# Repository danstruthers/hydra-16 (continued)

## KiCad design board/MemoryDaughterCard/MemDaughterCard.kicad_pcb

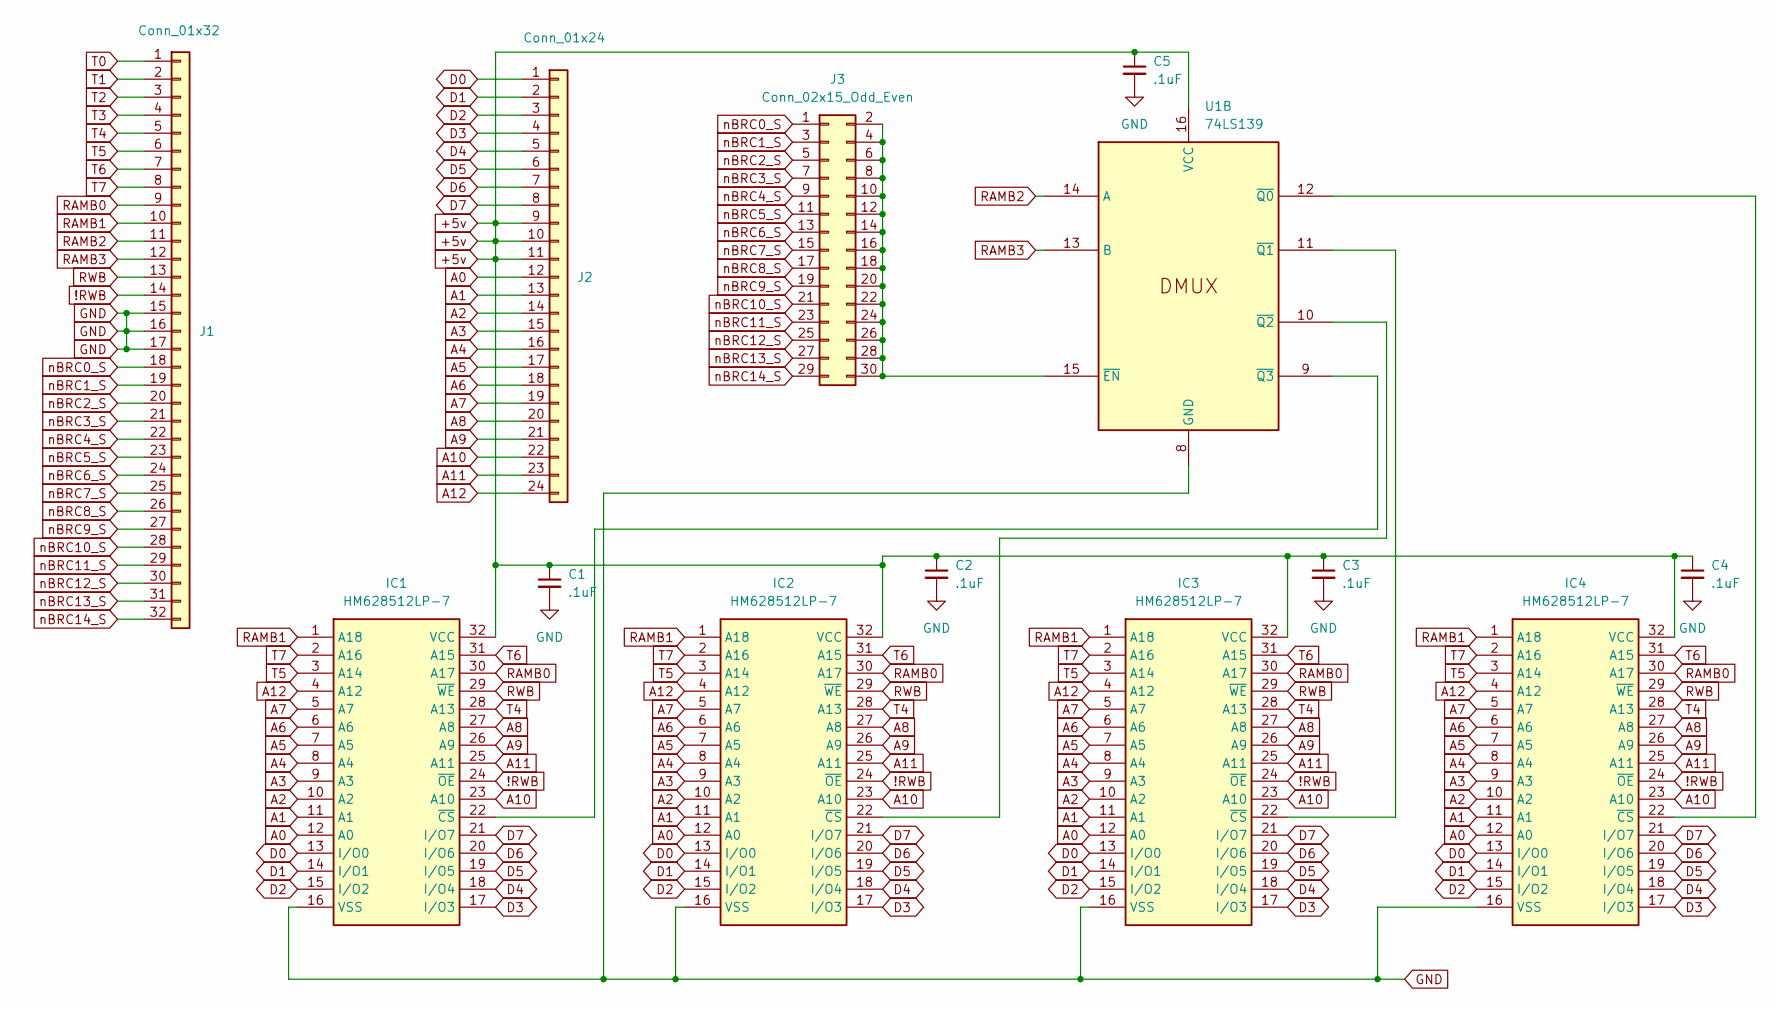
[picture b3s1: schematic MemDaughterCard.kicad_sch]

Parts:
C1, C2, C3, C4, C5: .1uF; C_Disc_D5.0mm_W2.5mm_P5.00mm
IC1, IC2, IC3, IC4: HM628512LP-7; DIP-32_W15.24mm_Socket_LongPads; Manufacturer_Part_Number HM628512LFP-7
J1: Conn_01x32; PinHeader_1x32_P2.54mm_Vertical
J2: Conn_01x24; PinHeader_1x24_P2.54mm_Vertical
J3: Conn_02x15_Odd_Even; PinHeader_2x15_P2.54mm_Vertical
U1: 74LS139; DIP-16_W7.62mm

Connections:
!RWB: IC1.24 (~OE), IC2.24 (~OE), IC3.24 (~OE), IC4.24 (~OE), J1.14
+5v: C1.1, C2.1, C3.1, C4.1, C5.1, IC1.32 (VCC), IC2.32 (VCC), IC3.32 (VCC), IC4.32 (VCC), J2.9, J2.10, J2.11, U1.16 (VCC)
A0: IC1.12 (A0), IC2.12 (A0), IC3.12 (A0), IC4.12 (A0), J2.12
A1: IC1.11 (A1), IC2.11 (A1), IC3.11 (A1), IC4.11 (A1), J2.13
A2: IC1.10 (A2), IC2.10 (A2), IC3.10 (A2), IC4.10 (A2), J2.14
A3: IC1.9 (A3), IC2.9 (A3), IC3.9 (A3), IC4.9 (A3), J2.15
A4: IC1.8 (A4), IC2.8 (A4), IC3.8 (A4), IC4.8 (A4), J2.16
A5: IC1.7 (A5), IC2.7 (A5), IC3.7 (A5), IC4.7 (A5), J2.17
A6: IC1.6 (A6), IC2.6 (A6), IC3.6 (A6), IC4.6 (A6), J2.18
A7: IC1.5 (A7), IC2.5 (A7), IC3.5 (A7), IC4.5 (A7), J2.19
A8: IC1.27 (A8), IC2.27 (A8), IC3.27 (A8), IC4.27 (A8), J2.20
A9: IC1.26 (A9), IC2.26 (A9), IC3.26 (A9), IC4.26 (A9), J2.21
A10: IC1.23 (A10), IC2.23 (A10), IC3.23 (A10), IC4.23 (A10), J2.22
A11: IC1.25 (A11), IC2.25 (A11), IC3.25 (A11), IC4.25 (A11), J2.23
A12: IC1.4 (A12), IC2.4 (A12), IC3.4 (A12), IC4.4 (A12), J2.24
D0: IC1.13 (I/O0), IC2.13 (I/O0), IC3.13 (I/O0), IC4.13 (I/O0), J2.1
D1: IC1.14 (I/O1), IC2.14 (I/O1), IC3.14 (I/O1), IC4.14 (I/O1), J2.2
D2: IC1.15 (I/O2), IC2.15 (I/O2), IC3.15 (I/O2), IC4.15 (I/O2), J2.3
D3: IC1.17 (I/O3), IC2.17 (I/O3), IC3.17 (I/O3), IC4.17 (I/O3), J2.4
D4: IC1.18 (I/O4), IC2.18 (I/O4), IC3.18 (I/O4), IC4.18 (I/O4), J2.5
D5: IC1.19 (I/O5), IC2.19 (I/O5), IC3.19 (I/O5), IC4.19 (I/O5), J2.6
D6: IC1.20 (I/O6), IC2.20 (I/O6), IC3.20 (I/O6), IC4.20 (I/O6), J2.7
D7: IC1.21 (I/O7), IC2.21 (I/O7), IC3.21 (I/O7), IC4.21 (I/O7), J2.8
GND: C1.2, C2.2, C3.2, C4.2, C5.2, IC1.16 (VSS), IC2.16 (VSS), IC3.16 (VSS), IC4.16 (VSS), J1.15, J1.16, J1.17, U1.8 (GND)
unnamed: IC1.22 (~CS), U1.9 (~Q3)
unnamed: IC2.22 (~CS), U1.10 (~Q2)
unnamed: IC3.22 (~CS), U1.11 (~Q1)
unnamed: IC4.22 (~CS), U1.12 (~Q0)
unnamed: J3.2, J3.4, J3.6, J3.8, J3.10, J3.12, J3.14, J3.16, J3.18, J3.20, J3.22, J3.24, J3.26, J3.28, J3.30, U1.15 (~EN)
RAMB0: IC1.30 (A17), IC2.30 (A17), IC3.30 (A17), IC4.30 (A17), J1.9
RAMB1: IC1.1 (A18), IC2.1 (A18), IC3.1 (A18), IC4.1 (A18), J1.10
RAMB2: J1.11, U1.14 (A)
RAMB3: J1.12, U1.13 (B)
RWB: IC1.29 (~WE), IC2.29 (~WE), IC3.29 (~WE), IC4.29 (~WE), J1.13
T0: J1.1
T1: J1.2
T2: J1.3
T3: J1.4
T4: IC1.28 (A13), IC2.28 (A13), IC3.28 (A13), IC4.28 (A13), J1.5
T5: IC1.3 (A14), IC2.3 (A14), IC3.3 (A14), IC4.3 (A14), J1.6
T6: IC1.31 (A15), IC2.31 (A15), IC3.31 (A15), IC4.31 (A15), J1.7
T7: IC1.2 (A16), IC2.2 (A16), IC3.2 (A16), IC4.2 (A16), J1.8
nBRC0_S: J1.18, J3.1
nBRC1_S: J1.19, J3.3
nBRC2_S: J1.20, J3.5
nBRC3_S: J1.21, J3.7
nBRC4_S: J1.22, J3.9
nBRC5_S: J1.23, J3.11
nBRC6_S: J1.24, J3.13
nBRC7_S: J1.25, J3.15
nBRC8_S: J1.26, J3.17
nBRC9_S: J1.27, J3.19
nBRC10_S: J1.28, J3.21
nBRC11_S: J1.29, J3.23
nBRC12_S: J1.30, J3.25
nBRC13_S: J1.31, J3.27
nBRC14_S: J1.32, J3.29

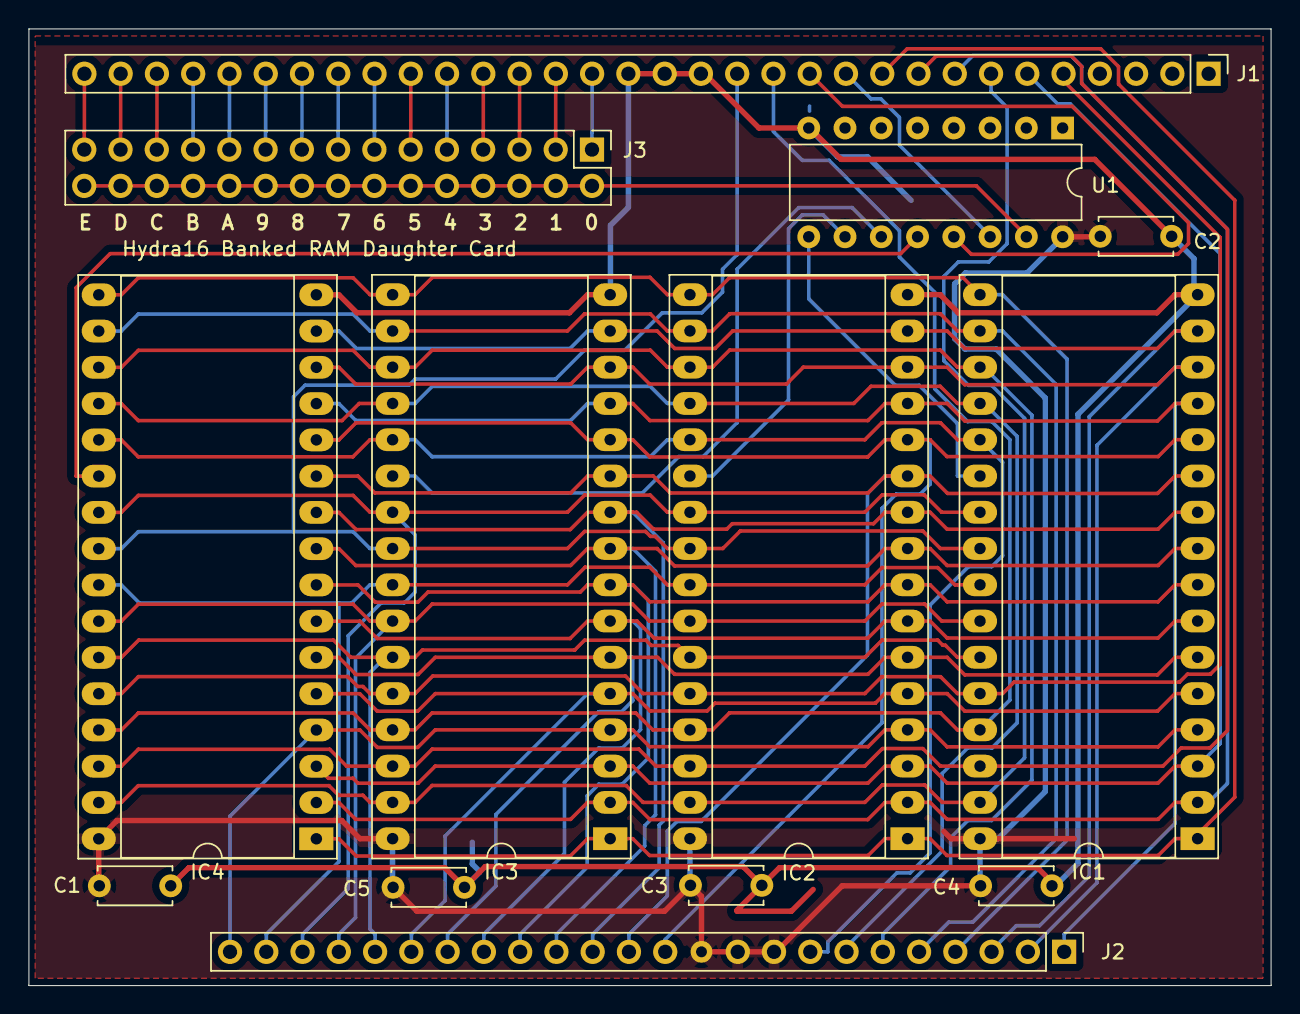
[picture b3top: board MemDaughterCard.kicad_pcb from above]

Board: 2 copper layers, 87.0 x 67.0 mm, 13 parts (0 on the bottom side), 53 nets.

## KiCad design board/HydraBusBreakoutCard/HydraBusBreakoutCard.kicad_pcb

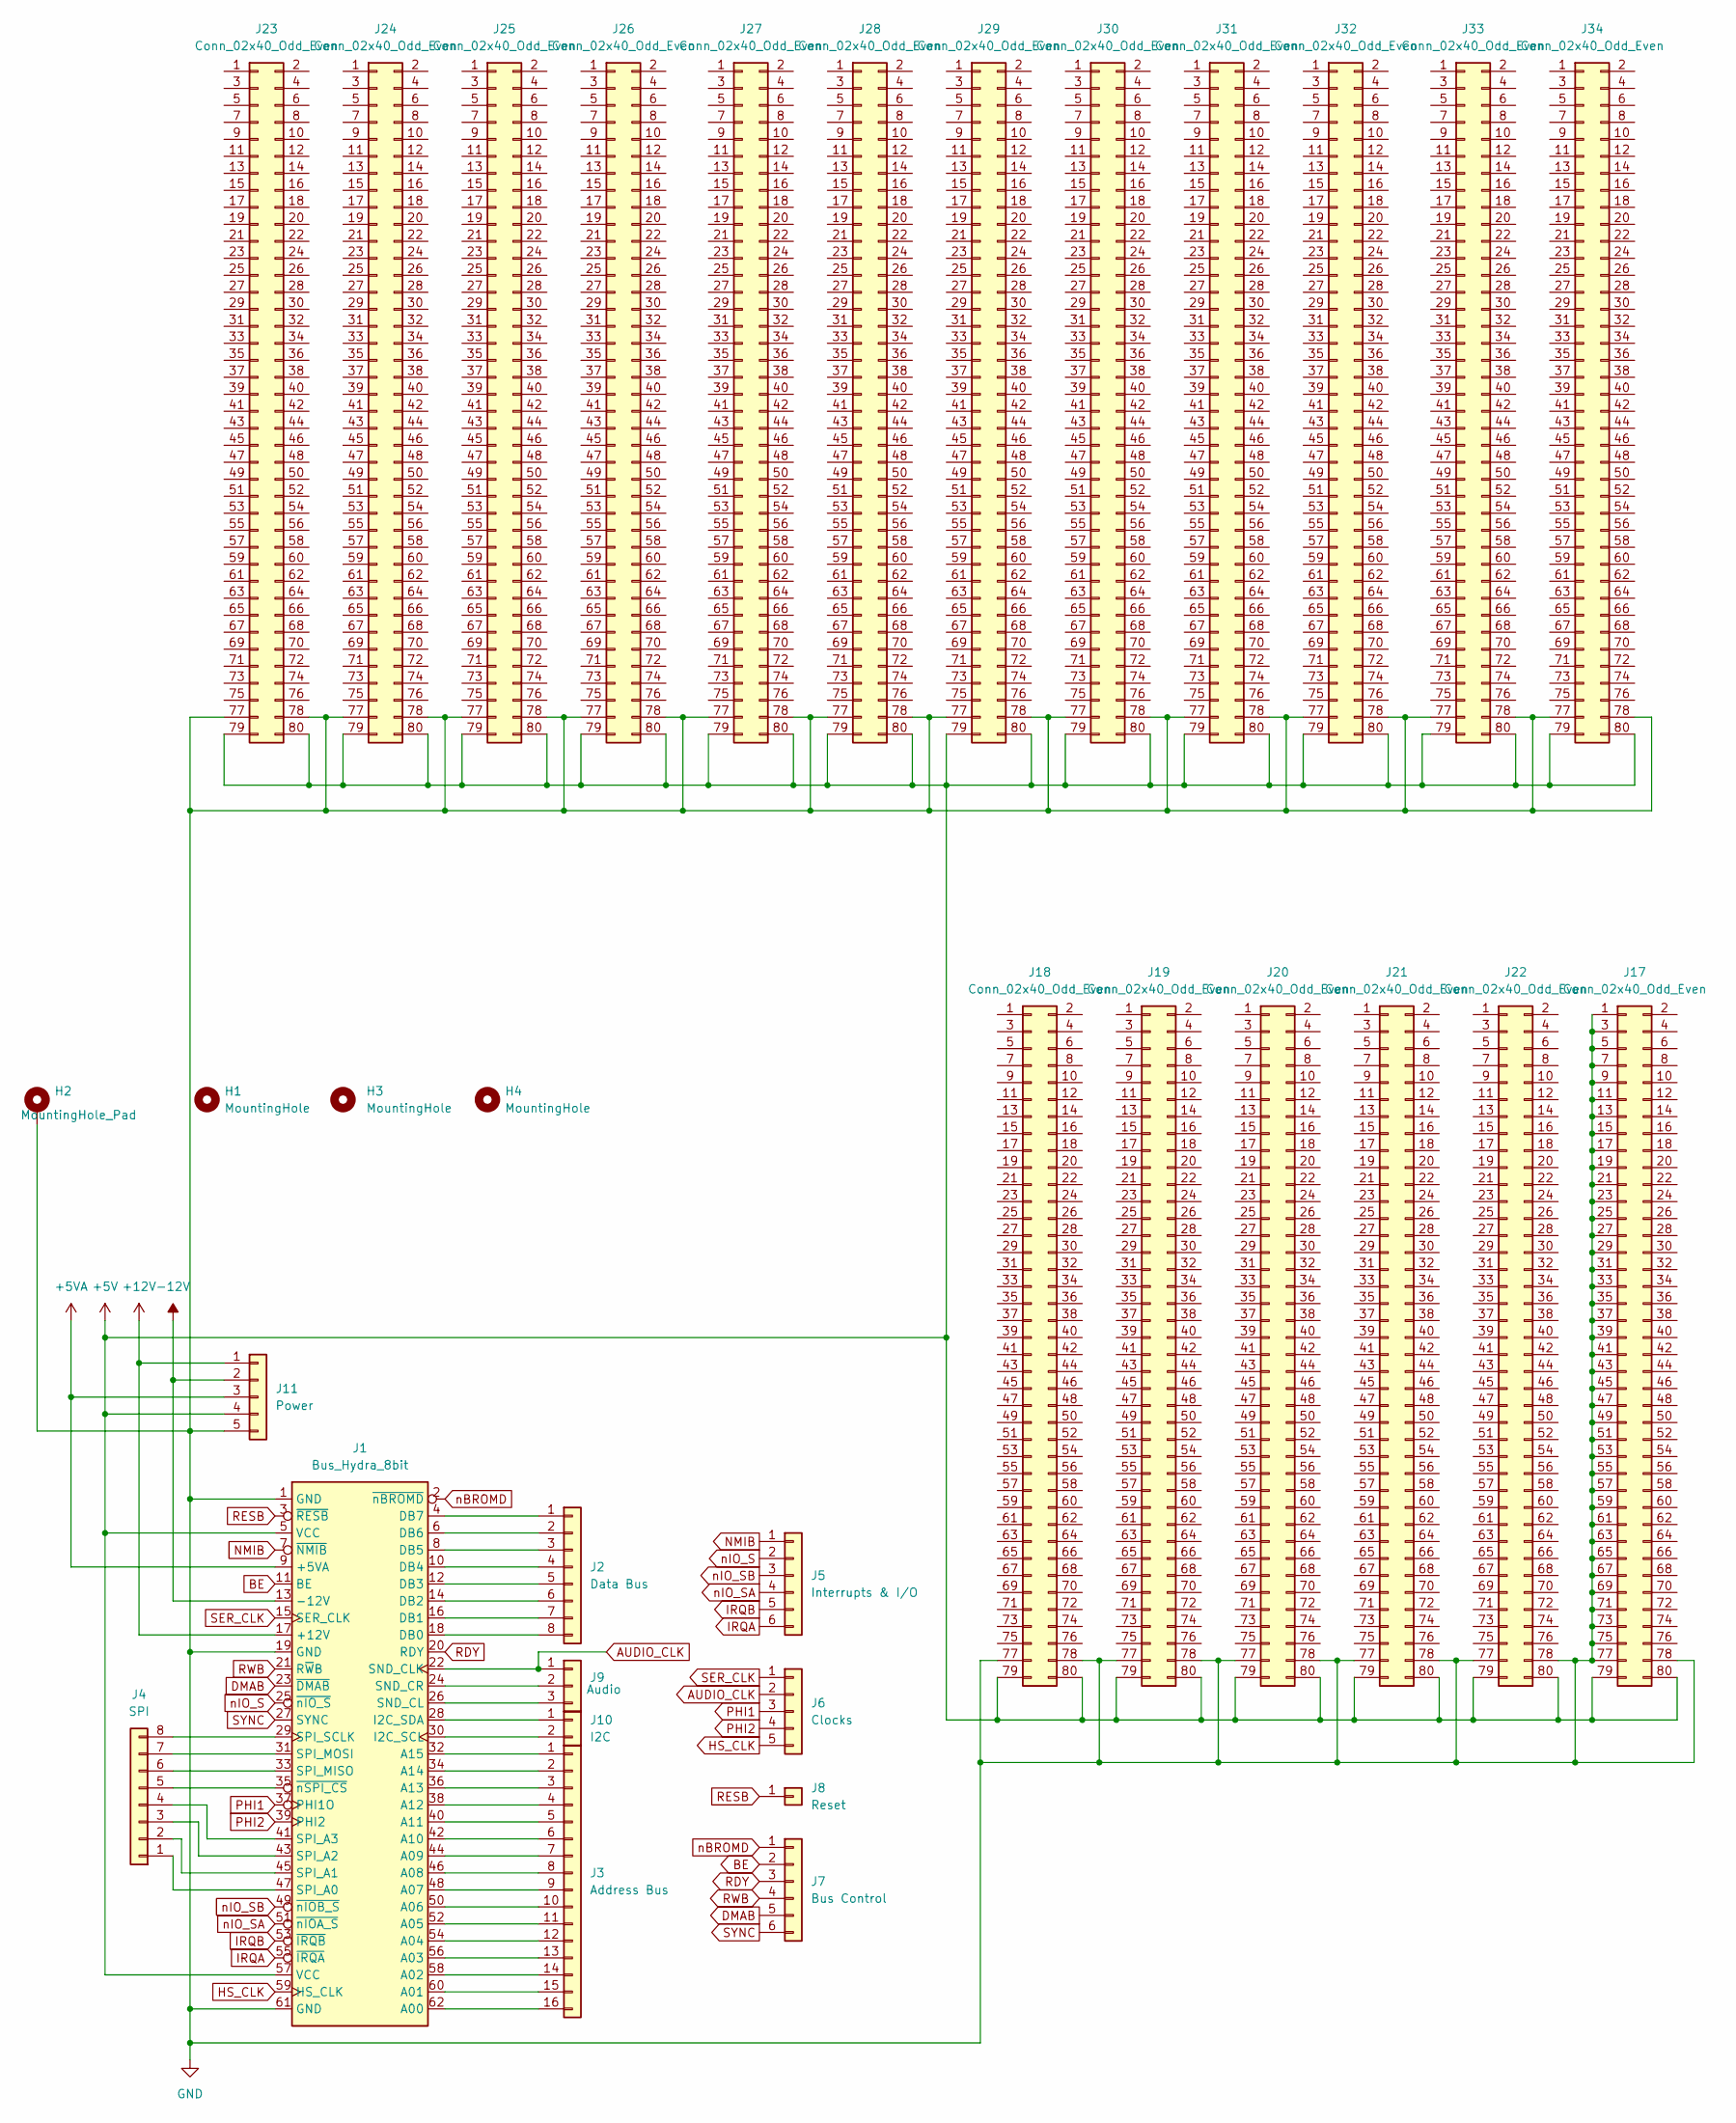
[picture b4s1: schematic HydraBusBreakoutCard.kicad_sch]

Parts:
H1, H3, H4: MountingHole; MountingHole_3.2mm_M3
H2: MountingHole_Pad; MountingHole_3.2mm_M3_ISO7380_Pad_TopBottom
J1: Bus_Hydra_8bit; BUS_Hydra_8Bit
J2: Data Bus; PinHeader_1x08_P2.54mm_Vertical
J3: Address Bus; PinHeader_1x16_P2.54mm_Vertical
J4: SPI; PinHeader_1x08_P2.54mm_Vertical
J5: Interrupts & I/O; PinHeader_1x06_P2.54mm_Vertical
J6: Clocks; PinHeader_1x05_P2.54mm_Vertical
J7: Bus Control; PinHeader_1x06_P2.54mm_Vertical
J8: Reset; PinHeader_1x01_P2.54mm_Vertical
J9: Audio; PinHeader_1x03_P2.54mm_Vertical
J10: I2C; PinHeader_1x02_P2.54mm_Vertical
J11: Power; PinHeader_1x05_P2.54mm_Vertical
J17, J18, J19, J20, J21, J22, J23, J24, J25, J26, J27, J28, J29, J30, J31, J32, J33, J34: Conn_02x40_Odd_Even; PinHeader_2x40_P2.54mm_Vertical

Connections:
+5V: J1.5 (VCC), J1.57 (VCC), J11.4, J17.79, J17.80, J18.79, J18.80, J19.79, J19.80, J20.79, J20.80, J21.79, J21.80, J22.79, J22.80, J23.79, J23.80, J24.79, J24.80, J25.79, J25.80, J26.79, J26.80, J27.79, J27.80, J28.79, J28.80, J29.79, J29.80, J30.79, J30.80, J31.79, J31.80, J32.79, J32.80, J33.79, J33.80, J34.79, J34.80
+5VA: J1.9 (+5VA), J11.3
+12V: J1.17 (+12V), J11.1
-12V: J1.13 (-12V), J11.2
AUDIO_CLK: J1.22 (SND_CLK), J6.2, J9.1
BE: J1.11 (BE), J7.2
DMAB: J1.23 (~DMAB), J7.5
GND: H2.1, J1.1 (GND), J1.19 (GND), J1.61 (GND), J11.5, J17.1, J17.3, J17.5, J17.7, J17.9, J17.11, J17.13, J17.15, J17.17, J17.19, J17.21, J17.23, J17.25, J17.27, J17.29, J17.31, J17.33, J17.35, J17.37, J17.39, J17.41, J17.43, J17.45, J17.47, J17.49, J17.51, J17.53, J17.55, J17.57, J17.59, J17.61, J17.63, J17.65, J17.67, J17.69, J17.71, J17.73, J17.75, J17.77, J17.78, J18.77, J18.78, J19.77, J19.78, J20.77, J20.78, J21.77, J21.78, J22.77, J22.78, J23.77, J23.78, J24.77, J24.78, J25.77, J25.78, J26.77, J26.78, J27.77, J27.78, J28.77, J28.78, J29.77, J29.78, J30.77, J30.78, J31.77, J31.78, J32.77, J32.78, J33.77, J33.78, J34.77, J34.78
HS_CLK: J1.59 (HS_CLK), J6.5
IRQA: J1.55 (~IRQA), J5.6
IRQB: J1.53 (~IRQB), J5.5
NMIB: J1.7 (~NMIB), J5.1
unnamed: J1.62 (A00), J3.16
unnamed: J1.60 (A01), J3.15
unnamed: J1.58 (A02), J3.14
unnamed: J1.56 (A03), J3.13
unnamed: J1.54 (A04), J3.12
unnamed: J1.52 (A05), J3.11
unnamed: J1.50 (A06), J3.10
unnamed: J1.48 (A07), J3.9
unnamed: J1.46 (A08), J3.8
unnamed: J1.44 (A09), J3.7
unnamed: J1.42 (A10), J3.6
unnamed: J1.40 (A11), J3.5
unnamed: J1.38 (A12), J3.4
unnamed: J1.36 (A13), J3.3
unnamed: J1.34 (A14), J3.2
unnamed: J1.32 (A15), J3.1
unnamed: J1.18 (DB0), J2.8
unnamed: J1.16 (DB1), J2.7
unnamed: J1.14 (DB2), J2.6
unnamed: J1.12 (DB3), J2.5
unnamed: J1.10 (DB4), J2.4
unnamed: J1.8 (DB5), J2.3
unnamed: J1.6 (DB6), J2.2
unnamed: J1.4 (DB7), J2.1
unnamed: J1.30 (I2C_SCL), J10.2
unnamed: J1.28 (I2C_SDA), J10.1
unnamed: J1.26 (SND_CL), J9.3
unnamed: J1.24 (SND_CR), J9.2
unnamed: J1.47 (SPI_A0), J4.1
unnamed: J1.45 (SPI_A1), J4.2
unnamed: J1.43 (SPI_A2), J4.3
unnamed: J1.41 (SPI_A3), J4.4
unnamed: J1.33 (SPI_MISO), J4.6
unnamed: J1.31 (SPI_MOSI), J4.7
unnamed: J1.29 (SPI_SCLK), J4.8
unnamed: J1.35 (~nSPI_CS), J4.5
PHI1: J1.37 (PHI1O), J6.3
PHI2: J1.39 (PHI2), J6.4
RDY: J1.20 (RDY), J7.3
RESB: J1.3 (~RESB), J8.1
RWB: J1.21 (R~WB), J7.4
SER_CLK: J1.15 (SER_CLK), J6.1
SYNC: J1.27 (SYNC), J7.6
nBROMD: J1.2 (~nBROMD), J7.1
nIO_S: J1.25 (~nIO_S), J5.2
nIO_SA: J1.51 (~nIOA_S), J5.4
nIO_SB: J1.49 (~nIOB_S), J5.3

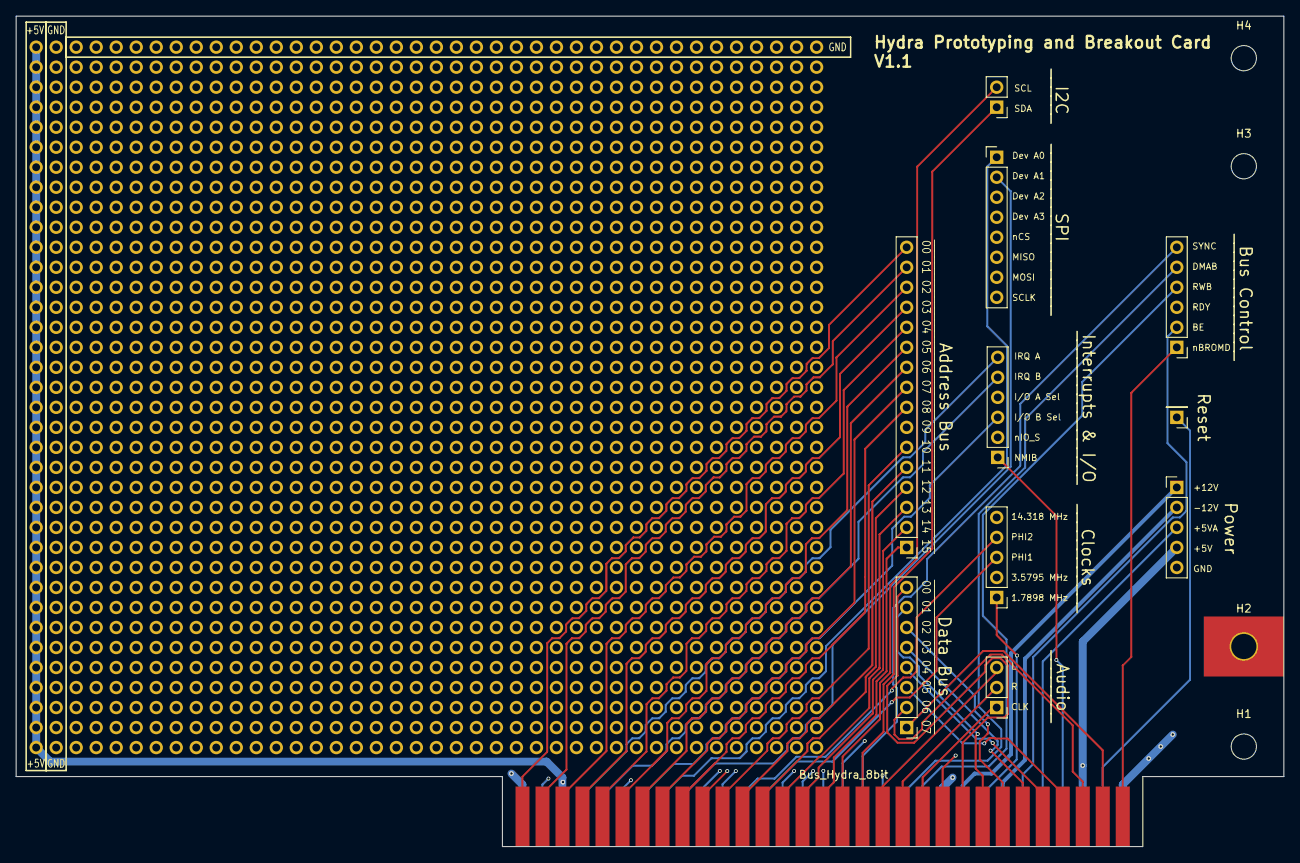
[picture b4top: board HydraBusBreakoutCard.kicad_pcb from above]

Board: 4 copper layers, 160.9 x 105.4 mm, 33 parts (0 on the bottom side), 59 nets.

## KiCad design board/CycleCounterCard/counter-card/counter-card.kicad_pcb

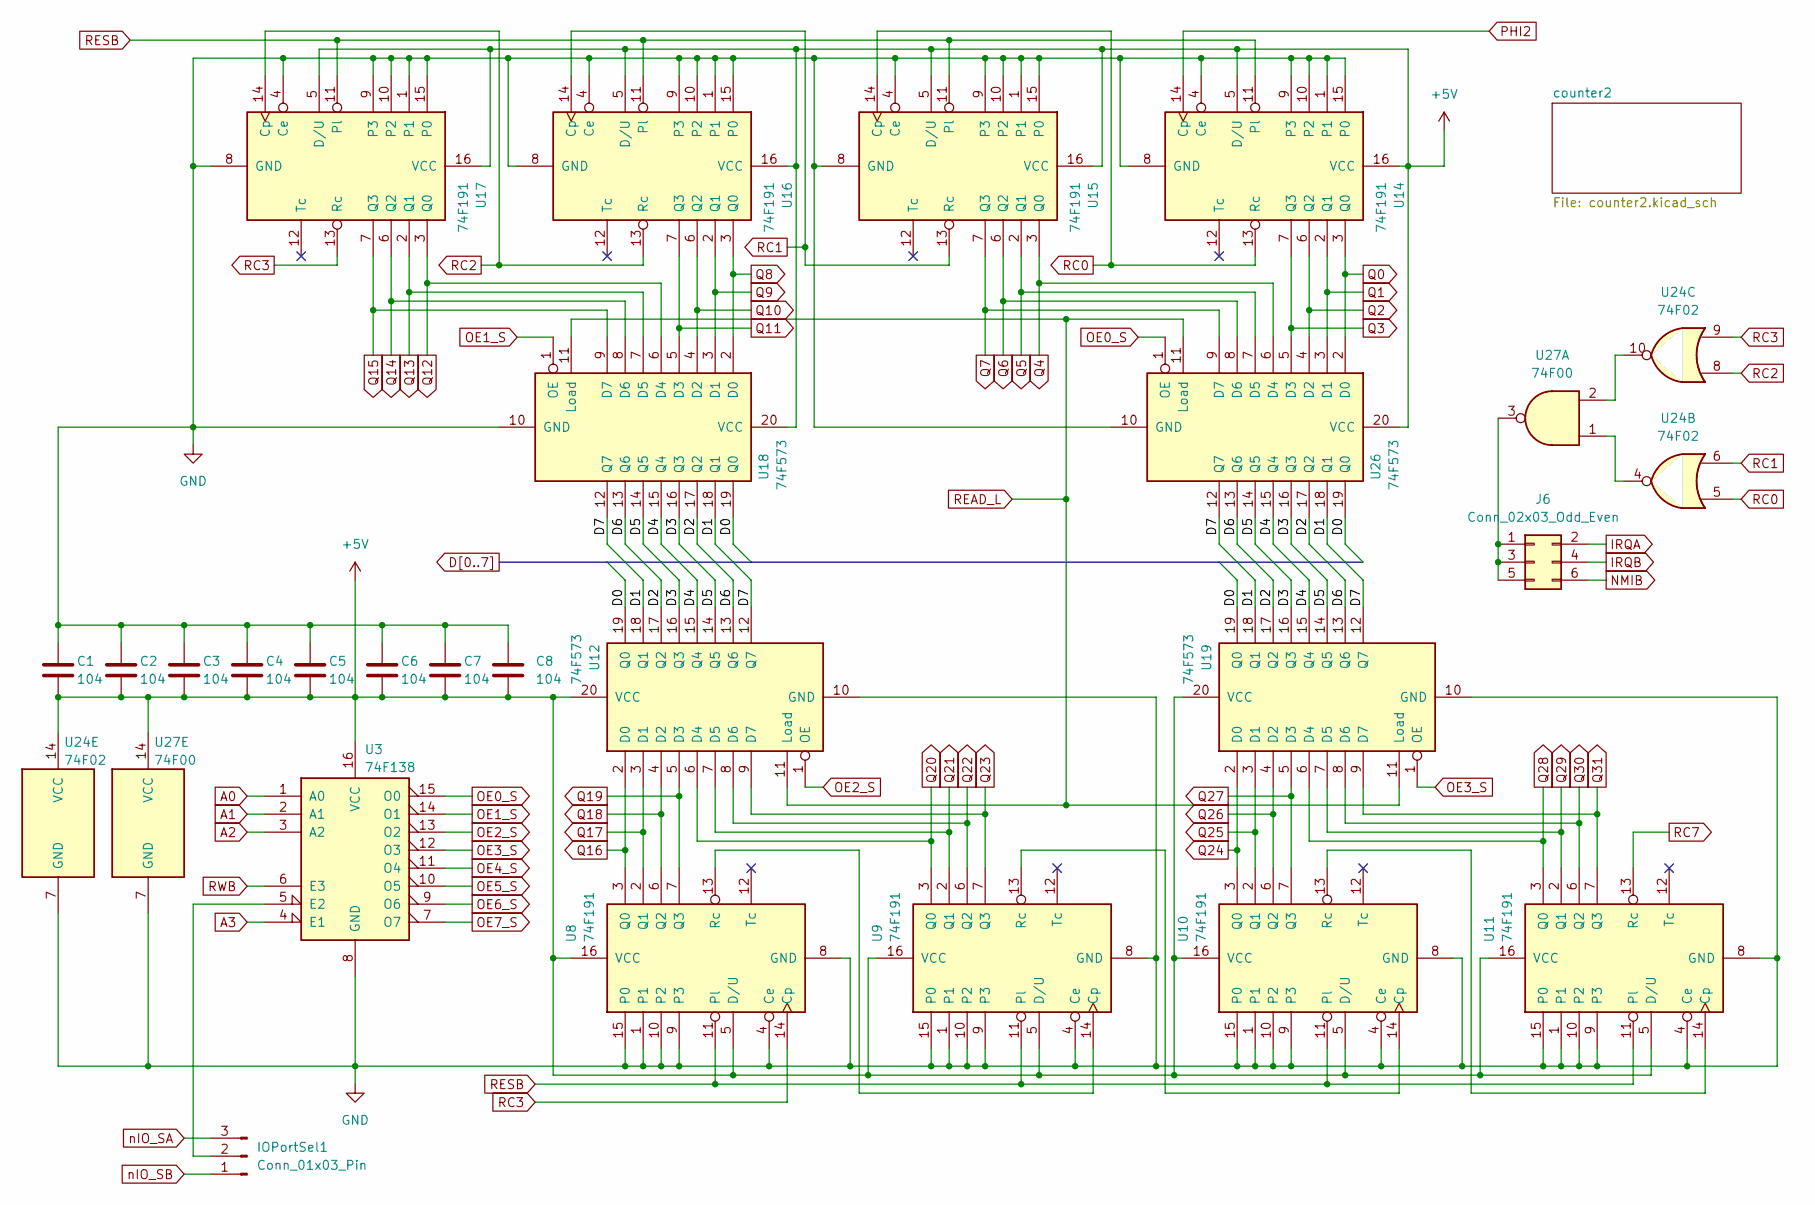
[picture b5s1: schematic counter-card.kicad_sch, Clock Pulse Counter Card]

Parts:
C1, C2, C3, C4, C5, C6, C7, C8: 104; C_Disc_D5.0mm_W2.5mm_P5.00mm
IOPortSel1: Conn_01x03_Pin; PinHeader_1x03_P2.54mm_Vertical
J6: Conn_02x03_Odd_Even; PinHeader_2x03_P2.54mm_Vertical
U3: 74F138; DIP-16_W7.62mm_Socket_LongPads
U8, U9, U10, U11, U14, U15, U16, U17: 74F191; DIP-16_W7.62mm_Socket_LongPads
U12, U18, U19, U26: 74F573; DIP-20_W7.62mm_Socket_LongPads
U24: 74F02; DIP-14_W7.62mm_Socket_LongPads
U27: 74F00; DIP-14_W7.62mm_Socket_LongPads

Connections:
+5V: C1.2, C2.2, C3.2, C4.2, C5.2, C6.2, C7.2, C8.2, U3.16 (VCC), U8.5 (D/U), U8.16 (VCC), U9.5 (D/U), U9.16 (VCC), U10.5 (D/U), U10.16 (VCC), U11.5 (D/U), U11.16 (VCC), U12.20 (VCC), U14.5 (D/U), U14.16 (VCC), U15.5 (D/U), U15.16 (VCC), U16.5 (D/U), U16.16 (VCC), U17.5 (D/U), U17.16 (VCC), U18.20 (VCC), U19.20 (VCC), U24.14 (VCC), U26.20 (VCC), U27.14 (VCC); also elsewhere on the board
A0: U3.1 (A0); also elsewhere on the board
A1: U3.2 (A1); also elsewhere on the board
A2: U3.3 (A2); also elsewhere on the board
A3: U3.4 (E1); also elsewhere on the board
D0: U12.19 (Q0), U18.19 (Q0), U19.19 (Q0), U26.19 (Q0); also elsewhere on the board
D1: U12.18 (Q1), U18.18 (Q1), U19.18 (Q1), U26.18 (Q1); also elsewhere on the board
D2: U12.17 (Q2), U18.17 (Q2), U19.17 (Q2), U26.17 (Q2); also elsewhere on the board
D3: U12.16 (Q3), U18.16 (Q3), U19.16 (Q3), U26.16 (Q3); also elsewhere on the board
D4: U12.15 (Q4), U18.15 (Q4), U19.15 (Q4), U26.15 (Q4); also elsewhere on the board
D5: U12.14 (Q5), U18.14 (Q5), U19.14 (Q5), U26.14 (Q5); also elsewhere on the board
D6: U12.13 (Q6), U18.13 (Q6), U19.13 (Q6), U26.13 (Q6); also elsewhere on the board
D7: U12.12 (Q7), U18.12 (Q7), U19.12 (Q7), U26.12 (Q7); also elsewhere on the board
GND: C1.1, C2.1, C3.1, C4.1, C5.1, C6.1, C7.1, C8.1, U3.8 (GND), U8.1, U8.4 (Ce), U8.8 (GND), U8.9 (P3), U8.10 (P2), U8.15 (P0), U9.1, U9.4 (Ce), U9.8 (GND), U9.9 (P3), U9.10 (P2), U9.15 (P0), U10.1, U10.4 (Ce), U10.8 (GND), U10.9 (P3), U10.10 (P2), U10.15 (P0), U11.1, U11.4 (Ce), U11.8 (GND), U11.9 (P3), U11.10 (P2), U11.15 (P0), U12.10 (GND), U14.1, U14.4 (Ce), U14.8 (GND), U14.9 (P3), U14.10 (P2), U14.15 (P0), U15.1, U15.4 (Ce), U15.8 (GND), U15.9 (P3), U15.10 (P2), U15.15 (P0), U16.1, U16.4 (Ce), U16.8 (GND), U16.9 (P3), U16.10 (P2), U16.15 (P0), U17.1, U17.4 (Ce), U17.8 (GND), U17.9 (P3), U17.10 (P2), U17.15 (P0), U18.10 (GND), U19.10 (GND), U24.7 (GND), U26.10 (GND), U27.7 (GND); also elsewhere on the board
IRQA: J6.2; also elsewhere on the board
IRQB: J6.4; also elsewhere on the board
NMIB: J6.6; also elsewhere on the board
unnamed: IOPortSel1.2, U3.5 (E2)
unnamed: J6.1, J6.3, J6.5, U27.3
unnamed: U8.13 (Rc), U9.14 (Cp)
unnamed: U9.13 (Rc), U10.14 (Cp)
unnamed: U10.13 (Rc), U11.14 (Cp)
unnamed: U24.4, U27.1
unnamed: U24.10, U27.2
OE0_S: U3.15 (O0), U26.1 (OE); also elsewhere on the board
OE1_S: U3.14 (O1), U18.1 (OE)
OE2_S: U3.13 (O2), U12.1 (OE)
OE3_S: U3.12 (O3), U19.1 (OE)
OE4_S: U3.11 (O4); also elsewhere on the board
OE5_S: U3.10 (O5); also elsewhere on the board
OE6_S: U3.9 (O6); also elsewhere on the board
OE7_S: U3.7 (O7); also elsewhere on the board
PHI2: U14.14 (Cp); also elsewhere on the board
Q0: U14.3 (Q0), U26.2 (D0); also elsewhere on the board
Q1: U14.2 (Q1), U26.3 (D1); also elsewhere on the board
Q2: U14.6 (Q2), U26.4 (D2); also elsewhere on the board
Q3: U14.7 (Q3), U26.5 (D3); also elsewhere on the board
Q4: U15.3 (Q0), U26.6 (D4); also elsewhere on the board
Q5: U15.2 (Q1), U26.7 (D5); also elsewhere on the board
Q6: U15.6 (Q2), U26.8 (D6); also elsewhere on the board
Q7: U15.7 (Q3), U26.9 (D7); also elsewhere on the board
Q8: U16.3 (Q0), U18.2 (D0); also elsewhere on the board
Q9: U16.2 (Q1), U18.3 (D1); also elsewhere on the board
Q10: U16.6 (Q2), U18.4 (D2); also elsewhere on the board
Q11: U16.7 (Q3), U18.5 (D3); also elsewhere on the board
Q12: U17.3 (Q0), U18.6 (D4); also elsewhere on the board
Q13: U17.2 (Q1), U18.7 (D5); also elsewhere on the board
Q14: U17.6 (Q2), U18.8 (D6); also elsewhere on the board
Q15: U17.7 (Q3), U18.9 (D7); also elsewhere on the board
Q16: U8.3 (Q0), U12.2 (D0); also elsewhere on the board
Q17: U8.2 (Q1), U12.3 (D1); also elsewhere on the board
Q18: U8.6 (Q2), U12.4 (D2); also elsewhere on the board
Q19: U8.7 (Q3), U12.5 (D3); also elsewhere on the board
Q20: U9.3 (Q0), U12.6 (D4); also elsewhere on the board
Q21: U9.2 (Q1), U12.7 (D5); also elsewhere on the board
Q22: U9.6 (Q2), U12.8 (D6); also elsewhere on the board
Q23: U9.7 (Q3), U12.9 (D7); also elsewhere on the board
Q24: U10.3 (Q0), U19.2 (D0); also elsewhere on the board
Q25: U10.2 (Q1), U19.3 (D1); also elsewhere on the board
Q26: U10.6 (Q2), U19.4 (D2); also elsewhere on the board
Q27: U10.7 (Q3), U19.5 (D3); also elsewhere on the board
Q28: U11.3 (Q0), U19.6 (D4); also elsewhere on the board
Q29: U11.2 (Q1), U19.7 (D5); also elsewhere on the board
Q30: U11.6 (Q2), U19.8 (D6); also elsewhere on the board
Q31: U11.7 (Q3), U19.9 (D7); also elsewhere on the board
RC0: U14.13 (Rc), U15.14 (Cp), U24.5
RC1: U15.13 (Rc), U16.14 (Cp), U24.6
RC2: U16.13 (Rc), U17.14 (Cp), U24.8
RC3: U8.14 (Cp), U17.13 (Rc), U24.9
RC7: U11.13 (Rc); also elsewhere on the board
READ_L: U12.11 (Load), U18.11 (Load), U19.11 (Load), U26.11 (Load); also elsewhere on the board
RESB: U8.11 (Pl), U9.11 (Pl), U10.11 (Pl), U11.11 (Pl), U14.11 (Pl), U15.11 (Pl), U16.11 (Pl), U17.11 (Pl); also elsewhere on the board
RWB: U3.6 (E3); also elsewhere on the board
nIO_SA: IOPortSel1.3; also elsewhere on the board
nIO_SB: IOPortSel1.1; also elsewhere on the board
